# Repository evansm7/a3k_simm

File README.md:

# Acorn A3000 4MB SIMM adapter board

25 Nov 2021

This board allows an Acorn A3000 computer to be upgraded to 4MB of RAM using a (still) common 4MB 72-pin SIMM.

Designed in Eagle.  Schematic [here](doc/simm_adapter_schematic.pdf), board layout [here](doc/simm_adapter_board.pdf).

Snazzy purple PCB c/o JLCPCB's 2-layer PCB service.

## SIMM compatibility

SIMMs are constructed with one bank (RAS0/RAS2 strobes) or two banks (RAS0-RAS3 strobes).

You will require a non-parity FPM or EDO 4MB SIMM with *one* bank.  Speed shouldn't matter, 70ns is fine.

Tested with a SIMM containing 2x TMS418169DZ 60ns EDO parts.

Ideally, look out for a SIMM with two chips, on one side.  Typically two-bank SIMMs have chips on both sides (but this is just a rule of thumb).

Because the unused RAS1/RAS3 strobes are tied inactive, you may find an 8MB dual-bank SIMM can be used with one (4MB) bank active, but this has not been tested.  A parity SIMM should also work (though the parity data lines are floating, which might not be great).  Again, untested.

Also, try to find a SIMM as short as possible, to avoid crashing into the case.  In extreme cases, the long pin headers on the A3000 motherboard could be trimmed or replaced...

## Construction

You will need:

   * 3x 0.1" 1x20 pin header sockets
   * 1x 72 pin vertical SIMM socket, such as a _TE Connectivity 5822021-4_
   * 2x Tantalum/SMT electrolytic capacitors.  Exact value isn't too important*.  10uF, 47uF, something like that. 

*: I noticed my SIMM doesn't have any decoupling on it whatsoever (but has footprints).  Cheeep.  You might want to add some more caps in the 0.1-1uF range, if this is the case.

A hole is provided in the middle for a bracket (not provided) that can attach to the nearby motherboard mounting hole, for stability.

## Licence

No warranty is provided, and this work is used at your own risk.  

Licenced as CC BY-SA 3.0

Copyright 2021 Matt Evans

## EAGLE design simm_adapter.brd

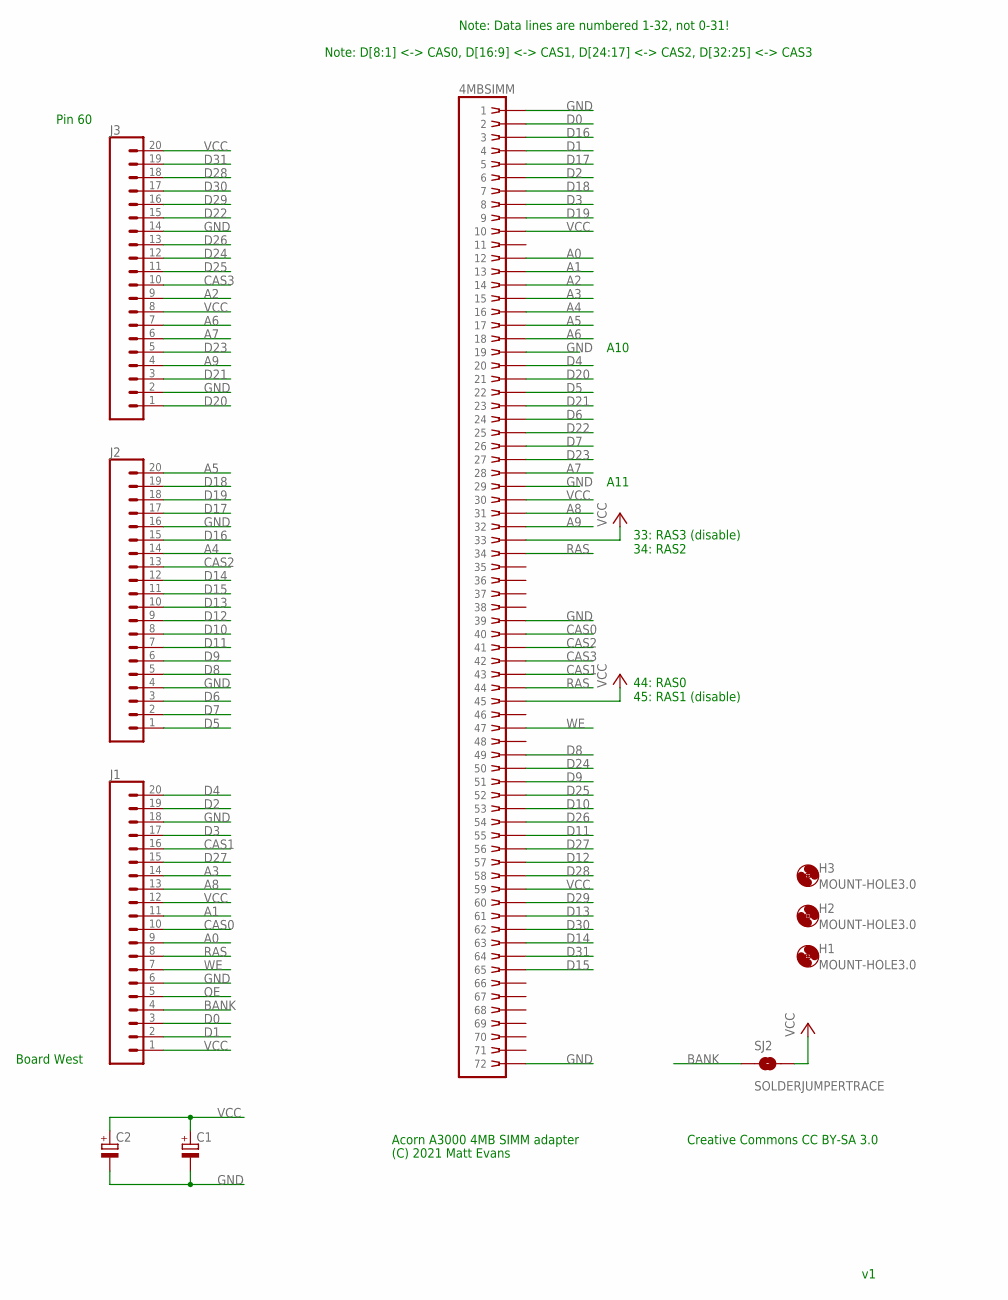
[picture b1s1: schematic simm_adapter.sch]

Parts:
4MBSIMM: SIMM72; 73826962
C1, C2: CPOL-EUCT7343; CT7343
H1, H2, H3: MOUNT-HOLE3.0; 3,0
J1, J2, J3: CONN_20; 1X20
SJ2: SOLDERJUMPERTRACE; SJ_2S-TRACE

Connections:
A0: 4MBSIMM.12, J1.9
A1: 4MBSIMM.13, J1.11
A2: 4MBSIMM.14, J3.9
A3: 4MBSIMM.15, J1.14
A4: 4MBSIMM.16, J2.14
A5: 4MBSIMM.17, J2.20
A6: 4MBSIMM.18, J3.7
A7: 4MBSIMM.28, J3.6
A8: 4MBSIMM.31, J1.13
A9: 4MBSIMM.32, J3.4
BANK: J1.4, SJ2.1
CAS0: 4MBSIMM.40, J1.10
CAS1: 4MBSIMM.43, J1.16
CAS2: 4MBSIMM.41, J2.13
CAS3: 4MBSIMM.42, J3.10
D0: 4MBSIMM.2, J1.3
D1: 4MBSIMM.4, J1.2
D2: 4MBSIMM.6, J1.19
D3: 4MBSIMM.8, J1.17
D4: 4MBSIMM.20, J1.20
D5: 4MBSIMM.22, J2.1
D6: 4MBSIMM.24, J2.3
D7: 4MBSIMM.26, J2.2
D8: 4MBSIMM.49, J2.5
D9: 4MBSIMM.51, J2.6
D10: 4MBSIMM.53, J2.8
D11: 4MBSIMM.55, J2.7
D12: 4MBSIMM.57, J2.9
D13: 4MBSIMM.61, J2.10
D14: 4MBSIMM.63, J2.12
D15: 4MBSIMM.65, J2.11
D16: 4MBSIMM.3, J2.15
D17: 4MBSIMM.5, J2.17
D18: 4MBSIMM.7, J2.19
D19: 4MBSIMM.9, J2.18
D20: 4MBSIMM.21, J3.1
D21: 4MBSIMM.23, J3.3
D22: 4MBSIMM.25, J3.15
D23: 4MBSIMM.27, J3.5
D24: 4MBSIMM.50, J3.12
D25: 4MBSIMM.52, J3.11
D26: 4MBSIMM.54, J3.13
D27: 4MBSIMM.56, J1.15
D28: 4MBSIMM.58, J3.18
D29: 4MBSIMM.60, J3.16
D30: 4MBSIMM.62, J3.17
D31: 4MBSIMM.64, J3.19
GND: 4MBSIMM.1, 4MBSIMM.19, 4MBSIMM.29, 4MBSIMM.39, 4MBSIMM.72, C1.-, C2.-, J1.6, J1.18, J2.4, J2.16, J3.2, J3.14
OE: J1.5
RAS: 4MBSIMM.34, 4MBSIMM.44, J1.8
VCC: 4MBSIMM.10, 4MBSIMM.30, 4MBSIMM.33, 4MBSIMM.45, 4MBSIMM.59, C1.+, C2.+, J1.1, J1.12, J3.8, J3.20, SJ2.2
WE: 4MBSIMM.47, J1.7

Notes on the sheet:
Pin 60
Board West
44: RAS0 45: RAS1 (disable)
33: RAS3 (disable) 34: RAS2
Note: Data lines are numbered 1-32, not 0-31!
Note: D[8:1] <-> CAS0, D[16:9] <-> CAS1, D[24:17] <-> CAS2, D[32:25] <-> CAS3
A10
A11
Acorn A3000 4MB SIMM adapter
(C) 2021 Matt Evans
Creative Commons CC BY-SA 3.0

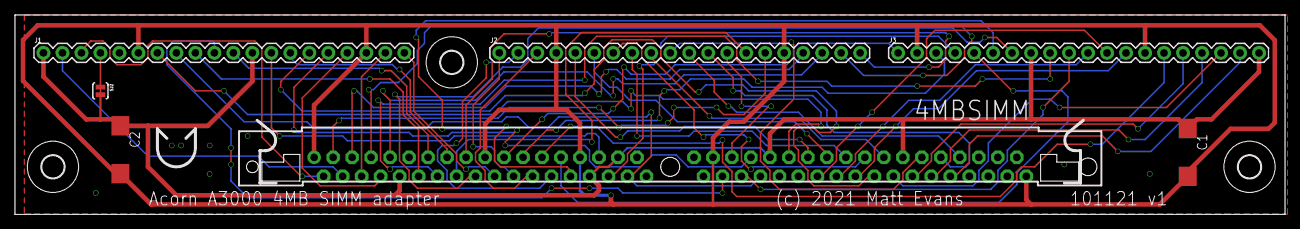
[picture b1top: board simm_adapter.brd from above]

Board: 2 copper layers, 169.8 x 26.7 mm, 10 parts (0 on the bottom side), 51 nets.

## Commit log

2021-11-10 v1 of SIMM adapter
    Fully routed (partially using messy autorouter), passes JLCPCB 2L DRC.
2021-11-25 Add v1 gerber files
2021-11-25 Add board/schematic PDFs
2021-11-25 Add README, picture

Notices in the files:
parts and their libraries:
SparkFun-Connectors: Licensing: Creative Commons ShareAlike 4.0 International - https://creativecommons.org/licenses/by-sa/4.0
